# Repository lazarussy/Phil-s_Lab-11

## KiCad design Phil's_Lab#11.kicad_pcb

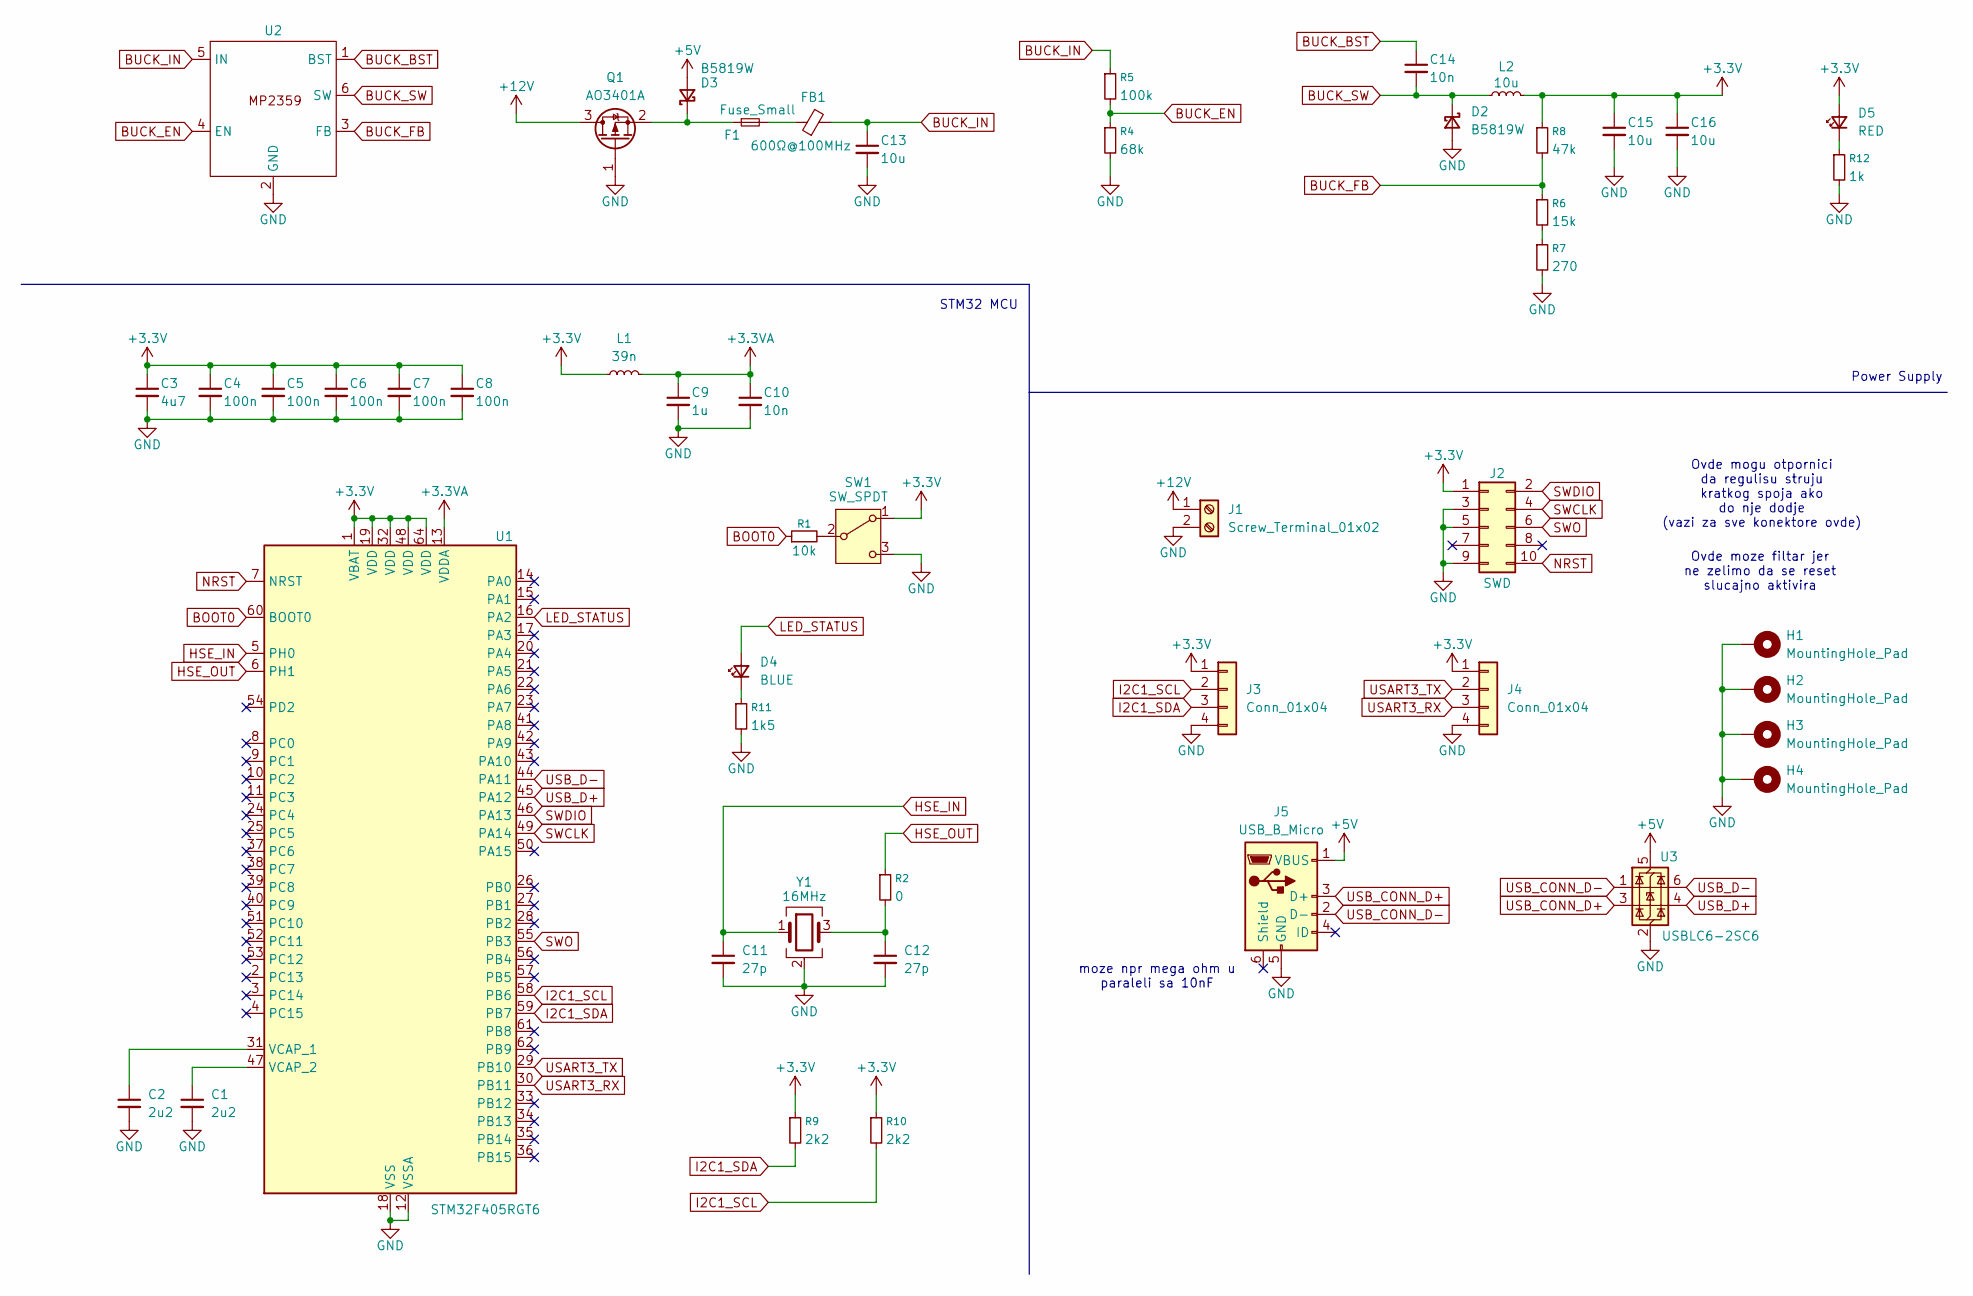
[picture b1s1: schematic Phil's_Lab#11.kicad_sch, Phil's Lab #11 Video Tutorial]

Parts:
C1, C2: 2u2; C_0603_1608Metric; LCSC Part # C23630
C3: 4u7; C_0603_1608Metric; LCSC Part # C19666
C4, C5, C6, C7, C8: 100n; C_0402_1005Metric; LCSC Part # C1525
C9: 1u; C_0402_1005Metric; LCSC Part # C52923
C10: 10n; C_0402_1005Metric; LCSC Part # C15195
C11, C12: 27p; C_0402_1005Metric; LCSC Part # C346183
C13, C15, C16: 10u; C_1206_3216Metric; LCSC Part # C13585
C14: 10n; C_1206_3216Metric; LCSC Part # C1846
D2, D3: B5819W; D_SOD-123; LCSC Part # C9900270134
D4: BLUE; LED_0603_1608Metric
D5: RED; LED_0603_1608Metric
F1: Fuse_Small; Fuse_1206_3216Metric
FB1: 600Ω@100MHz; L_0805_2012Metric; LCSC Part # C1002
H1, H2, H3, H4: MountingHole_Pad; MountingHole_4.3mm_M4_Pad_Via
J1: Screw_Terminal_01x02; TerminalBlock_Phoenix_PT-1,5-2-3.5-H_1x02_P3.50mm_Horizontal
J2: SWD; PinHeader_2x05_P1.27mm_Vertical_SMD
J3, J4: Conn_01x04; Molex_PicoBlade_53048-0410_1x04_P1.25mm_Horizontal
J5: USB_B_Micro; USB_Micro-B_Amphenol_10118193-0001LF_Horizontal
L1: 39n; L_0402_1005Metric; LCSC Part # C26443
L2: 10u; L_Sunlord_MWSA1204S-100; LCSC Part # C139506
Q1: AO3401A; SOT-23; LCSC Part # C15127
R1: 10k; R_0402_1005Metric; LCSC Part # C25744
R2: 0; R_0402_1005Metric; LCSC Part # C23231
R4: 68k; R_0603_1608Metric; LCSC Part # C25803
R5: 100k; R_0603_1608Metric; LCSC Part # C25803
R6: 15k; R_0603_1608Metric; LCSC Part # C22809
R7: 270; R_0603_1608Metric; LCSC Part # C22966
R8: 47k; R_0603_1608Metric; LCSC Part # C25819
R9, R10: 2k2; R_0402_1005Metric; LCSC Part # C25879
R11: 1k5; R_0201_0603Metric; LCSC Part # C22843
R12: 1k; R_0201_0603Metric; LCSC Part # C21190
SW1: SW_SPDT; SW_Slide-03_Wuerth-WS-SLTV_10x2.5x6.4_P2.54mm; LCSC Part # C22449121
U1: STM32F405RGT6; LQFP-64_10x10mm_P0.5mm; LCSC Part # C15742
U2: TSOT-23-6; LCSC Part # C14259
U3: USBLC6-2SC6; SOT-23-6; LCSC Part # C558442
Y1: 16MHz; Crystal_SMD_3225-4Pin_3.2x2.5mm; LCSC Part # C2905353

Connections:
+3.3V: C3.1, C4.1, C5.1, C6.1, C7.1, C8.1, C15.1, C16.1, D5.2 (A), J2.1, J3.1, J4.1, L1.1, L2.2, R8.1, R9.1, R10.1, SW1.1 (A), U1.1 (VBAT), U1.19 (VDD), U1.32 (VDD), U1.48 (VDD), U1.64 (VDD)
+3.3VA: C9.1, C10.1, L1.2, U1.13 (VDDA)
+5V: D3.2 (A), J5.1 (VBUS), U3.5 (VBUS)
+12V: J1.1, Q1.3 (D)
BOOT0: R1.1, U1.60 (BOOT0)
BUCK_BST: C14.1, U2.1 (BST)
BUCK_EN: R4.1, R5.2, U2.4 (EN)
BUCK_FB: R6.1, R8.2, U2.3 (FB)
BUCK_IN: C13.1, FB1.2, R5.1, U2.5 (IN)
BUCK_SW: C14.2, D2.1 (K), L2.1, U2.6 (SW)
GND: C1.2, C2.2, C3.2, C4.2, C5.2, C6.2, C7.2, C8.2, C9.2, C10.2, C11.2, C12.2, C13.2, C15.2, C16.2, D2.2 (A), H1.1 (1_1), H2.1 (1_1), H3.1 (1_1), H4.1 (1_1), J1.2, J2.3, J2.5, J2.9, J3.4, J4.4, J5.5 (GND), Q1.1 (G), R4.2, R7.2, R11.2, R12.2, SW1.3 (C), U1.12 (VSSA), U1.18 (VSS), U1.63 (VSS), U2.2 (GND), U3.2 (GND), Y1.2 (G), Y1.4 (G)
HSE_IN: C11.1, U1.5 (PH0), Y1.1
HSE_OUT: R2.1, U1.6 (PH1)
I2C1_SCL: J3.2, R10.2, U1.58 (PB6)
I2C1_SDA: J3.3, R9.2, U1.59 (PB7)
LED_STATUS: D4.2 (A), U1.16 (PA2)
NRST: J2.10, U1.7 (NRST)
unnamed: C12.1, R2.2, Y1.3
unnamed: D3.1 (K), F1.1, Q1.2 (S)
unnamed: D4.1 (K), R11.1
unnamed: D5.1 (K), R12.1
unnamed: F1.2, FB1.1
unnamed: R6.2, R7.1
unnamed: R1.2, SW1.2 (B)
unnamed: C2.1, U1.31 (VCAP_1)
unnamed: C1.1, U1.47 (VCAP_2)
SWCLK: J2.4, U1.49 (PA14)
SWDIO: J2.2, U1.46 (PA13)
SWO: J2.6, U1.55 (PB3)
USART3_RX: J4.3, U1.30 (PB11)
USART3_TX: J4.2, U1.29 (PB10)
USB_CONN_D+: J5.3 (D+), U3.3 (I/O2)
USB_CONN_D-: J5.2 (D-), U3.1 (I/O1)
USB_D+: U1.45 (PA12), U3.4 (I/O2)
USB_D-: U1.44 (PA11), U3.6 (I/O1)

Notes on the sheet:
moze npr mega ohm u paraleli sa 10nF
STM32 MCU
Ovde moze filtar jer ne zelimo da se reset slucajno aktivira
Power Supply
Ovde mogu otpornici da regulisu struju kratkog spoja ako do nje dodje (vazi za sve konektore ovde)

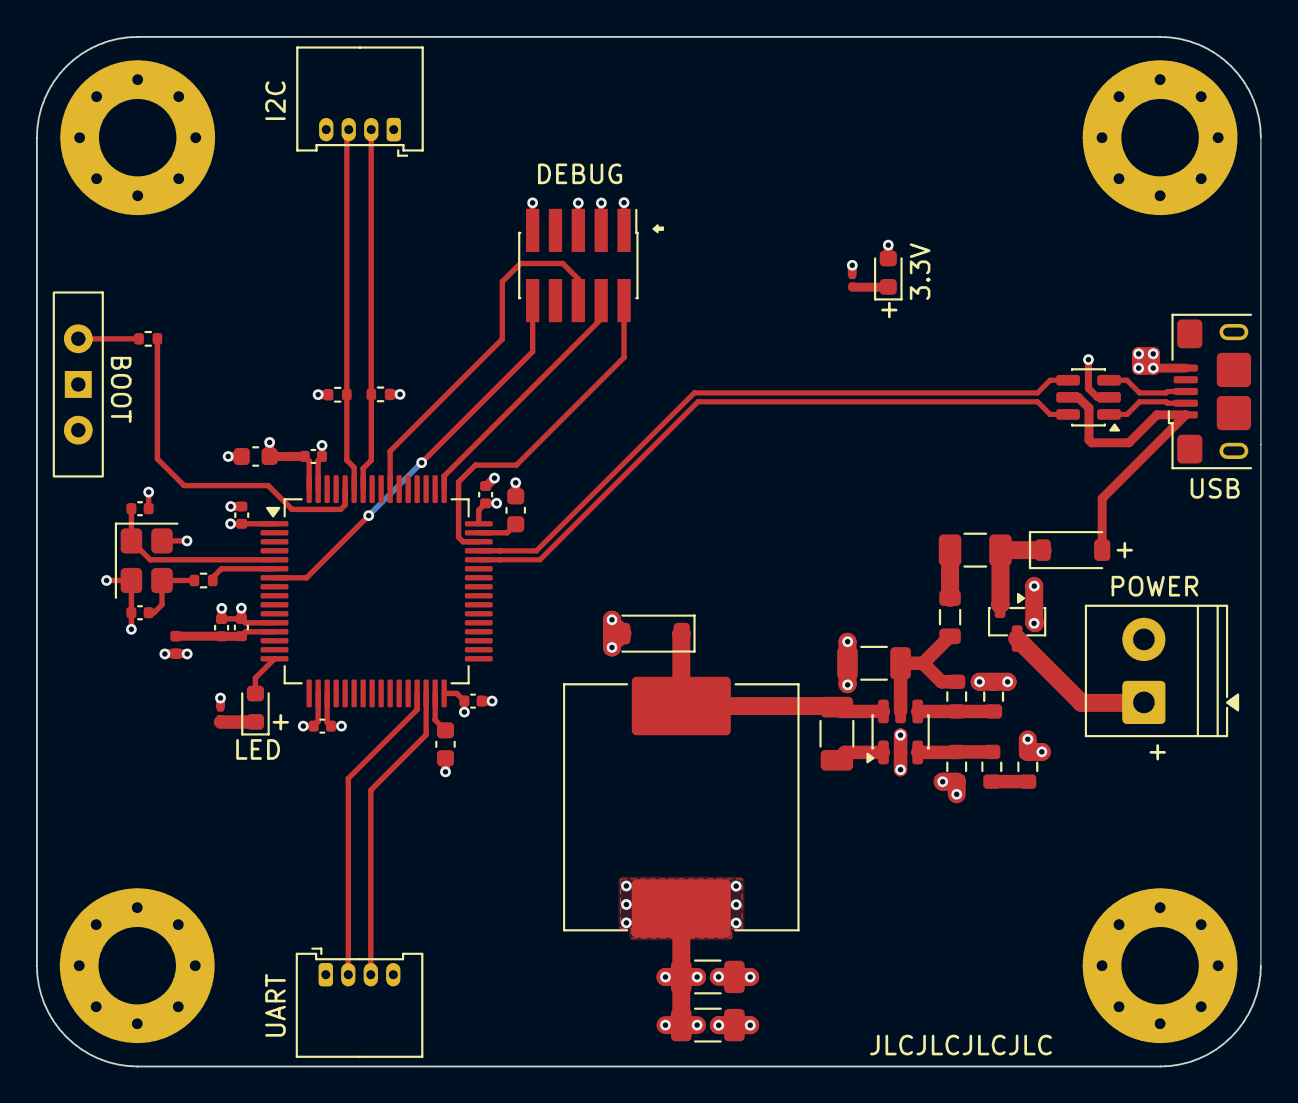
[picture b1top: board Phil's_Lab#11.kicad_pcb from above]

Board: 4 copper layers, 68.0 x 57.2 mm, 50 parts (0 on the bottom side), 35 nets.
